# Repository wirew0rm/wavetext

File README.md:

# wavetext
A very affordable POV Display for an etching and soldering workshop.

* Costs ~5€
* 10x5 Font, 62 Characters
* 10 Texts with 12 Characters each programmable
* Programmable from webpage by using a flickering image
* Detection of waving speed and direction

## Needed packages

 - avr-gcc
 - avr-libc
 - avrdude

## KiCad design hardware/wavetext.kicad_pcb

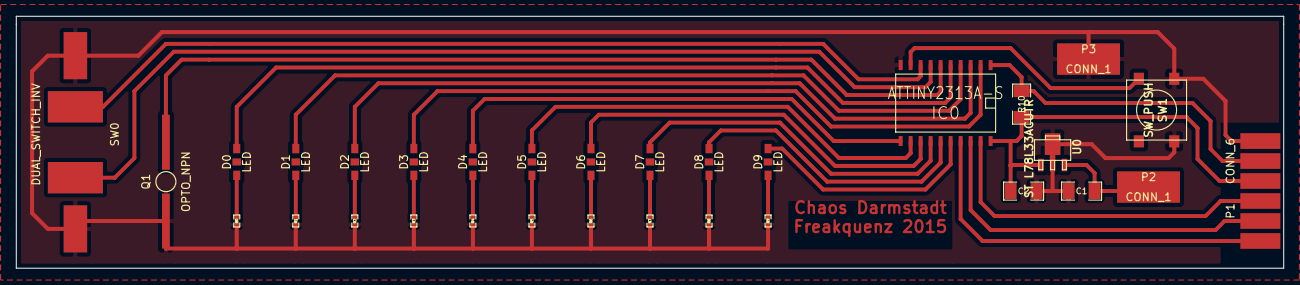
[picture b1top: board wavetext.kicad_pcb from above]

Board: 2 copper layers, 161.0 x 32.0 mm, 31 parts (0 on the bottom side), 31 nets.

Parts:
C1, C2: C; SM1206
D0, D1, D2, D3, D4, D5, D6, D7, D8, D9: LED
IC0: ATTINY2313A-S; SO20L
P1: CONN_6; PCBISP
P2, P3: CONN_1; Powerpad
Q1: OPTO_NPN; Fototransistor
R0, R1, R2, R3, R4, R5, R6, R7, R8, R9: 40; SM0402
R10: 1k; SM1206
SW0: DUAL_SWITCH_INV; Wackelschalter
SW1: SW_PUSH; SW_PUSH_SMD
U0: ST L78L33ACUTR; sot89

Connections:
GND: C1.2, C2.2, IC0.10, P1.6, P3.1, Q1.1, R0.2, R1.2, R2.2, R3.2, R4.2, R5.2, R6.2, R7.2, R8.2, R9.2, SW0.2, SW1.1, U0.2
unnamed: D2.1, IC0.3
unnamed: D8.1, IC0.15
unnamed: D7.1, IC0.14
unnamed: D6.1, IC0.13
unnamed: D5.1, IC0.12
unnamed: D4.1, IC0.11
unnamed: D3.1, IC0.2
unnamed: D1.1, IC0.4
unnamed: D0.1, IC0.5
unnamed: IC0.6, Q1.3
unnamed: IC0.9, SW1.2
unnamed: D9.1, IC0.16
unnamed: IC0.18, P1.2
unnamed: IC0.19, P1.3
unnamed: IC0.7, SW0.1
unnamed: IC0.8, SW0.3
unnamed: C2.1, IC0.20, P1.4, R10.1, U0.1
unnamed: IC0.1, P1.5, R10.2
unnamed: IC0.17, P1.1
unnamed: D7.2, R7.1
unnamed: D6.2, R6.1
unnamed: D5.2, R5.1
unnamed: D3.2, R3.1
unnamed: D2.2, R2.1
unnamed: D1.2, R1.1
unnamed: D0.2, R0.1
unnamed: D4.2, R4.1
unnamed: D9.2, R9.1
unnamed: D8.2, R8.1
VCC: C1.1, P2.1, U0.3

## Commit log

2015-06-29 Added board test
2015-06-29 Readme
2015-06-29 kicad projekt angelegt
2015-06-29 Activate all leds on button press, not the other way round
2015-06-30 changed design to use 10 microcontroller pins instead of 7
2015-07-07 completed schema and pcb layout
2015-07-07 improved schematic and pcb
2015-07-08 Wackelschalter footprint added
2015-07-08 firmware
2015-07-08 rearranged pcb parts
2015-07-08 Fixed pin numbering on wackelschalter.
    Completed wirering on pcb.
2015-07-08 changed led footprint
2015-07-09 PCB fertig
2015-07-09 written font tool
2015-07-09 Board als SVG
2015-07-09 fixed font tool
2015-07-09 added some debug code
2015-07-09 first version. static timing
2015-07-10 some improvements
2015-07-10 first version using the timer. does not work!
2015-07-10 Text changer sends Manchester coded blinking pattern in javascript
2015-07-10 PCB final, breitere Leiterbahnen, spannungsregler richtigrum
2015-07-10 font tool fixes
2015-07-10 static timing
2015-07-11 blah
2015-07-11 dos2unix
2015-07-11 README.md: add needed packages
2015-07-11 firmware/wavetext.c: code format, remove unused code
2015-07-11 remove firmware/debug.c
2015-07-11 udev rule for programmer
2015-07-11 firmware/wavetext.c: add comments
2015-07-11 alternatives timergedöns
2015-07-11 More or less working
2015-07-11 textchanger: use another protocol
    each bit takes 120ms to transmit.
    it starts with black. the duration of black determines if its a 0 (40ms) or a 1 (80ms)
